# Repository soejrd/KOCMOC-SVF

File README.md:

# KOCMOC SVF Filter - Custom Layout

This repository contains a modified version of the [KOCMOC SVF filter](https://github.com/janne808/Kocmoc-Eurorack), originally created by janne808.
The modifications include a new PCB layout and panel design that are intended to be more user-friendly and visually appealing, while preserving the core functionality of the original circuit.

## Credits

The original KOCMOC SVF filter was designed by janne808 and released under the [CERN Open Hardware Licence Version 2 - Strongly Reciprocal](https://ohwr.org/cernohl). I would like to thank janne808 for creating the original circuit and making it available under an open license, which allowed me to build upon it and create this modified version.

## Modifications

The modifications to the KOCMOC SVF filter consist of a new PCB layout and panel design, which were created to better fit my personal design system and style. Some of the specific changes include:

- Re-arranged and labeled the in- and outputs on the panel for readability.
- Changed the dimensions of the PCB and panel to better fit my preferred module size and layout.
- Updated the panel design to match my personal style, including typography and design elements.

## License

This modified version of the KOCMOC SVF filter is also released under the [CERN Open Hardware Licence Version 2 - Strongly Reciprocal](https://ohwr.org/cernohl), which requires that any modifications or derivatives of the original work are also released under the same license. This means that you are free to use, modify, and distribute this modified version as long as you comply with the terms of the license.

## Usage
> [!CAUTION]
> The frequency potentiometer is wired backwards, you'll have to modify this yourself.

If you want to use or build upon this modified version of the KOCMOC SVF filter, you can clone or download this repository and use the files as you would any other open hardware project. You will find all the necessary files, including schematics, PCB layout, and panel design in the "respected" folder. There are files included to manufacture the board, panel (and assembly) at JLCPCB. However, please note that not every part is supplied by JLC and you will need to source some of these parts yourself.

## Contributing

If you have any suggestions or improvements for this modified version of the KOCMOC SVF filter, feel free to open an issue or pull request on this repository.

## Acknowledgments

I would like to thank janne808 for creating the original KOCMOC SVF filter and releasing it under an open license, as well as the open (eurorack) hardware community for their contributions and support.

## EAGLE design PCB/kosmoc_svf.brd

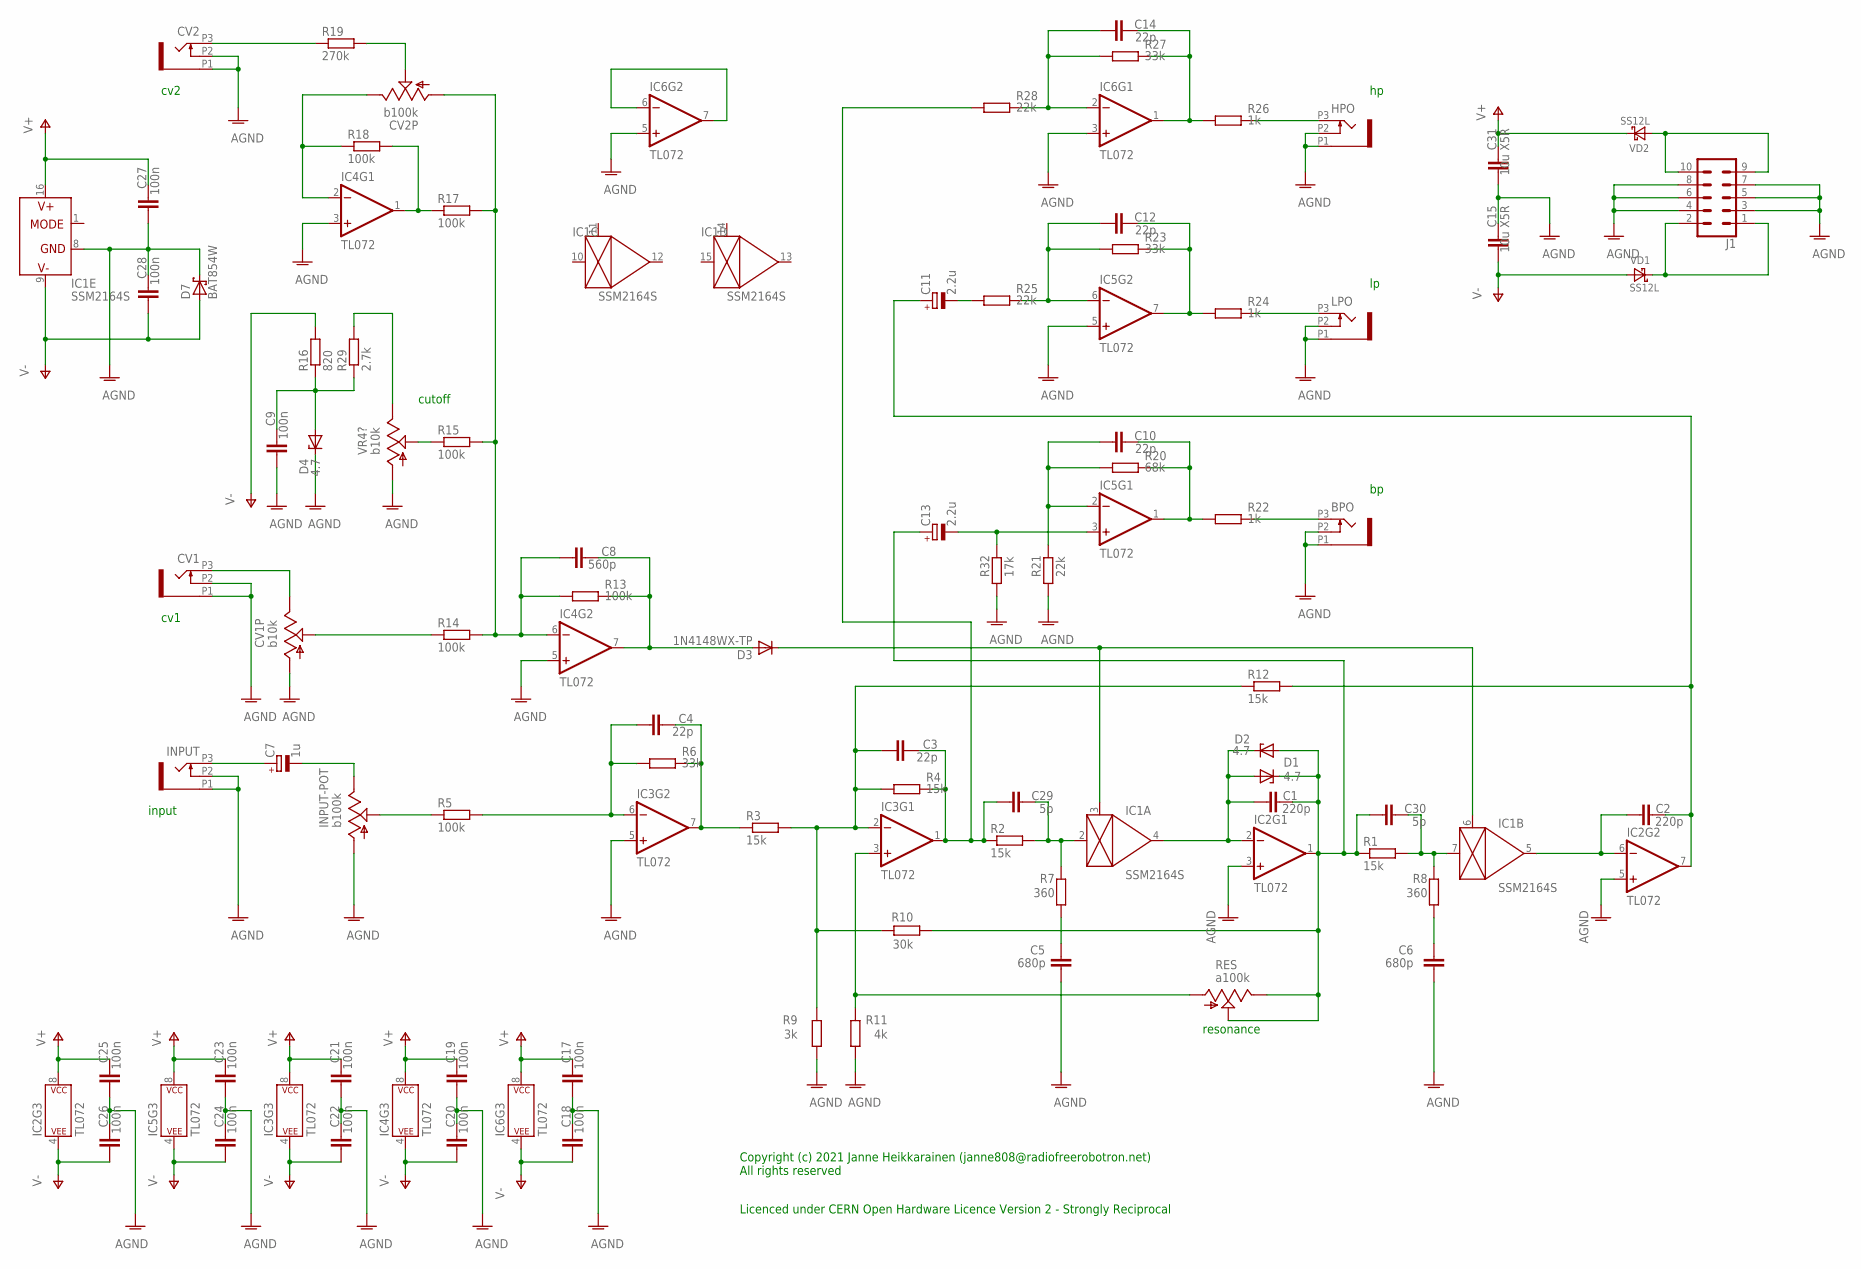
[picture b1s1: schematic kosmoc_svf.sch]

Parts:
BPO: PJ301_THONKICONN6; WQP_PJ_301M6
C1, C2: 220p; C0603
C3, C4, C10, C12, C14: 22p; C0603
C5, C6: 680p; C0603
C7: 1u; PANASONIC_B
C8: 560p; C0603
C9, C17, C18, C19, C20, C21, C22, C23, C24, C25, C26, C27, C28: 100n; C0603
C11, C13: 2.2u; PANASONIC_B
C15, C31: 10u X5R; C0805
C29, C30: 5p; C0603
CV1, CV2: PJ301_THONKICONN6; WQP_PJ_301M6
CV1P: b10k; ALPS_POT_VERTICAL_PS
CV2P: b100k; ALPS_POT_VERTICAL_PS
D1, D2, D4: 4.7; DIODE_SOD80C
D3: 1N4148WX-TP; SOD323R-INFINEON
D7: BAT854W; SOT323
HPO: PJ301_THONKICONN6; WQP_PJ_301M6
IC1: SSM2164S; SOIC16N
IC2, IC3, IC4, IC5, IC6: TL072; SO08
INPUT: PJ301_THONKICONN6; WQP_PJ_301M6
INPUT-POT: b100k; ALPS_POT_VERTICAL_PS
J1: CONN_05X2SHD; 2X5-SHROUDED
LPO: PJ301_THONKICONN6; WQP_PJ_301M6
R1, R2, R3, R4, R12: 15k; R0603
R5, R13, R14, R15, R17, R18: 100k; R0603
R6, R23, R27: 33k; R0603
R7, R8: 360; R0603
R9: 3k; R0603
R10: 30k; R0603
R11: 4k; R0603
R16: 820; R0603
R19: 270k; R0603
R20: 68k; R0603
R21, R25, R28: 22k; R0603
R22, R24, R26: 1k; R0603
R29: 2.7k; R0603
R32: 17k; R0603
RES: a100k; ALPS_POT_VERTICAL_PS
VD1, VD2: SS12L; SOD123
VR4?: b10k; ALPS_POT_VERTICAL_PS

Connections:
AGND: BPO.P1 (1), BPO.P2 (2), C5.1, C6.1, C9.1, C15.2, C17.1, C18.2, C19.1, C20.2, C21.1, C22.2, C23.1, C24.2, C25.1, C26.2, C27.1, C28.2, C31.1, CV1.P1 (1), CV1.P2 (2), CV1P.P$3 (A), CV2.P1 (1), CV2.P2 (2), D4.C, D7.3 (K), HPO.P1 (1), HPO.P2 (2), IC1.8 (GND), IC2.3 (+IN), IC2.5 (+IN), IC3.5 (+IN), IC4.3 (+IN), IC4.5 (+IN), IC5.5 (+IN), IC6.3 (+IN), IC6.5 (+IN), INPUT.P1 (1), INPUT.P2 (2), INPUT-POT.P$3 (A), J1.3, J1.4, J1.5, J1.6, J1.7, J1.8, LPO.P1 (1), LPO.P2 (2), R9.1, R11.1, R21.1, R32.1, VR4?.P$3 (A)
unnamed: C1.1, D1.A, D2.C, IC1.4 (OUT), IC2.2 (-IN)
unnamed: C2.1, IC1.5 (OUT), IC2.6 (-IN)
unnamed: R15.1, VR4?.P$2 (S)
unnamed: C30.2, IC1.7 (IN), R1.2, R8.2
unnamed: C3.2, C29.1, IC3.1 (OUT), R2.1, R4.2, R28.1
unnamed: C29.2, IC1.2 (IN), R2.2, R7.2
unnamed: C9.2, D4.A, R16.1, R29.1
unnamed: C4.2, IC3.7 (OUT), R3.1, R6.2
unnamed: C3.1, IC3.2 (-IN), R3.2, R4.1, R9.2, R10.2, R12.1
unnamed: C4.1, IC3.6 (-IN), R5.2, R6.1
unnamed: R29.2, VR4?.P$1 (E)
unnamed: C2.2, C11.+, IC2.7 (OUT), R12.2
unnamed: C7.-, INPUT-POT.P$1 (E)
unnamed: C7.+, INPUT.P3 (3)
unnamed: C5.2, R7.1
unnamed: C6.2, R8.1
unnamed: C8.2, D3.A, IC4.7 (OUT), R13.2
unnamed: D3.C, IC1.3 (CTRL), IC1.6 (CTRL)
unnamed: CV1P.P$2 (S), R14.1
unnamed: INPUT-POT.P$2 (S), R5.1
unnamed: CV1.P3 (3), CV1P.P$1 (E)
unnamed: HPO.P3 (3), R26.2
unnamed: IC4.1 (OUT), R17.1, R18.2
unnamed: LPO.P3 (3), R24.2
unnamed: BPO.P3 (3), R22.2
unnamed: C10.1, IC5.2 (-IN), R20.1, R21.2
unnamed: CV2.P3 (3), R19.1
unnamed: CV2P.P$2 (S), R19.2
unnamed: C10.2, IC5.1 (OUT), R20.2, R22.1
unnamed: C13.-, IC5.3 (+IN), R32.2
unnamed: C12.1, IC5.6 (-IN), R23.1, R25.2
unnamed: C12.2, IC5.7 (OUT), R23.2, R24.1
unnamed: C11.-, R25.1
unnamed: IC6.6 (-IN), IC6.7 (OUT)
unnamed: C14.2, IC6.1 (OUT), R26.1, R27.2
unnamed: C14.1, IC6.2 (-IN), R27.1, R28.2
unnamed: J1.1, J1.2, VD1.C
unnamed: J1.9, J1.10, VD2.A
TO_CV2_POT1: C8.1, CV2P.P$3 (A), IC4.6 (-IN), R13.1, R14.2, R15.2, R17.2
TO_CV2_POT2: CV2P.P$1 (E), IC4.2 (-IN), R18.1
TO_RESO_POT1: C1.2, C13.+, C30.1, D1.C, D2.A, IC2.1 (OUT), R1.1, R10.1, RES.P$1 (E), RES.P$2 (S)
TO_RESO_POT2: IC3.3 (+IN), R11.2, RES.P$3 (A)
V+: C17.2, C19.2, C21.2, C23.2, C25.2, C27.2, C31.2, IC1.16 (V+), IC2.8 (P$V+), IC3.8 (P$V+), IC4.8 (P$V+), IC5.8 (P$V+), IC6.8 (P$V+), VD2.C
V-: C15.1, C18.1, C20.1, C22.1, C24.1, C26.1, C28.1, D7.1 (A), IC1.9 (V-), IC2.4 (P$V-), IC3.4 (P$V-), IC4.4 (P$V-), IC5.4 (P$V-), IC6.4 (P$V-), R16.2, VD1.A

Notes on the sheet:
resonance
cutoff
input
cv1
cv2
Copyright (c) 2021 Janne Heikkarainen (janne808@radiofreerobotron.net) All rights reserved
Licenced under CERN Open Hardware Licence Version 2 - Strongly Reciprocal

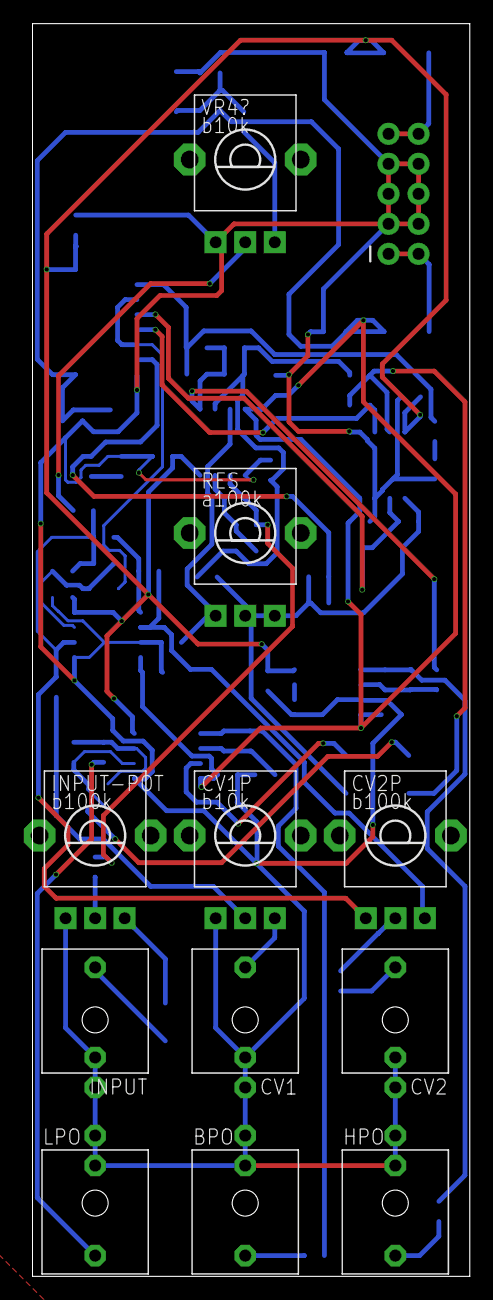
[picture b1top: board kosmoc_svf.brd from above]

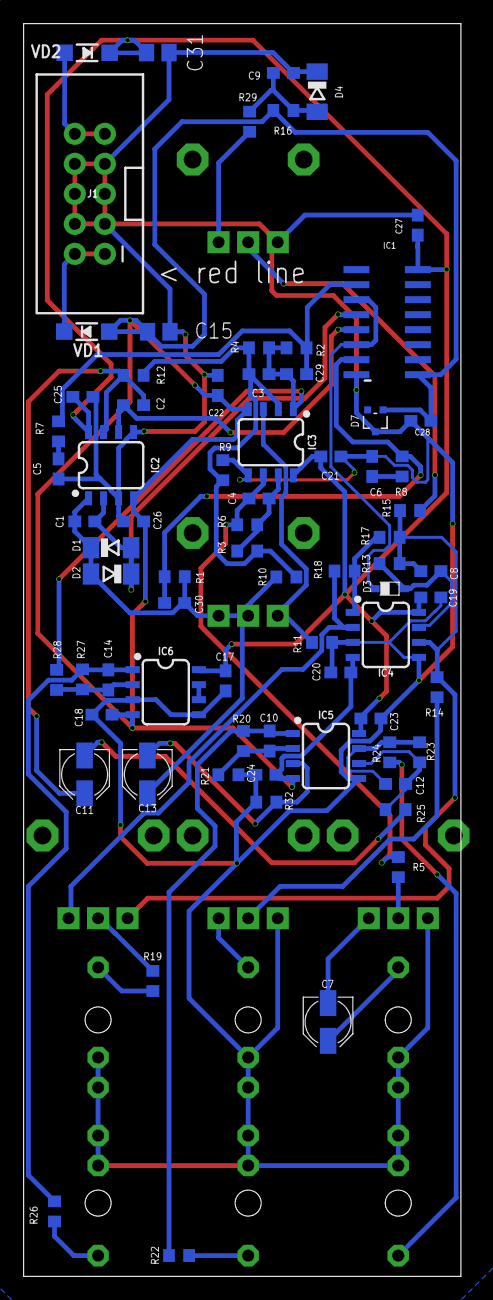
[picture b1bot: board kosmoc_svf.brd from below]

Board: 2 copper layers, 37.0 x 106.0 mm, 85 parts (74 on the bottom side), 45 nets.

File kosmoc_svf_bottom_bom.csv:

Comment,Designator,Footprint,LCSC Part #
1N4148WX-TP,D3,SOD323R-INFINEON,
1k,R22 R24 R26,R0603,
1u,C7,PANASONIC_B,
2.2u,C11 C13,PANASONIC_B,
2.7k,R29,R0603,
3k,R9,R0603,
4.7,D1 D2 D4,DIODE_SOD80C,
4k,R11,R0603,
5p,C29 C30,C0603,
10u X5R,C15 C31,C0805,
15k,R1 R2 R3 R4 R12,R0603,
17k,R32,R0603,
22k,R21 R25 R28,R0603,
22p,C3 C4 C10 C12 C14,C0603,
30k,R10,R0603,
33k,R6 R23 R27,R0603,
68k,R20,R0603,
100k,R5 R13 R14 R15 R17 R18,R0603,
100n,C9 C17 C18 C19 C20 C21 C22 C23 C24 C25 C26 C27 C28,C0603,
220p,C1 C2,C0603,
270k,R19,R0603,
360,R7 R8,R0603,
560p,C8,C0603,
680p,C5 C6,C0603,
820,R16,R0603,
BAT854W,D7,SOT323,
SS12L,VD1 VD2,SOD123,
SSM2164S,IC1,SOIC16N,
TL072,IC2 IC3 IC4 IC5 IC6,SO08,

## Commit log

2023-03-24 Original files uploaded
2023-03-24 Init description commit
2023-03-24 Changed files around
2023-03-24 Added image
2023-03-24 Added link
2023-03-24 Some text changes
2023-03-24 Mention JLC files
2023-03-24 Add license file
2023-03-28 Frequency potentiometer warning
2025-05-16 Update README.md
    Added better caution to readme

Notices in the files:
parts and their libraries:
SparkFun-IC-Amplifiers: Licensing: Creative Commons ShareAlike 4.0 International - https://creativecommons.org/licenses/by-sa/4.0
